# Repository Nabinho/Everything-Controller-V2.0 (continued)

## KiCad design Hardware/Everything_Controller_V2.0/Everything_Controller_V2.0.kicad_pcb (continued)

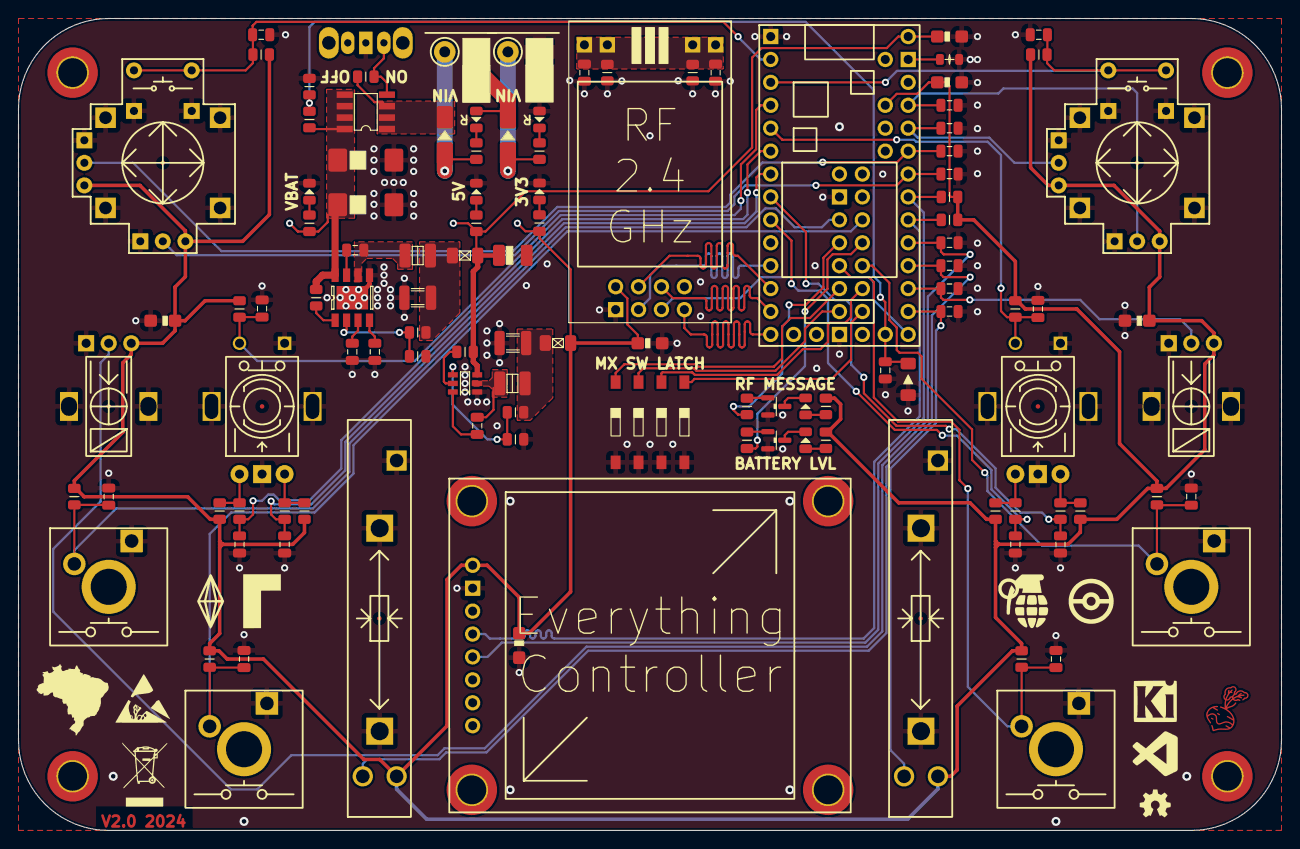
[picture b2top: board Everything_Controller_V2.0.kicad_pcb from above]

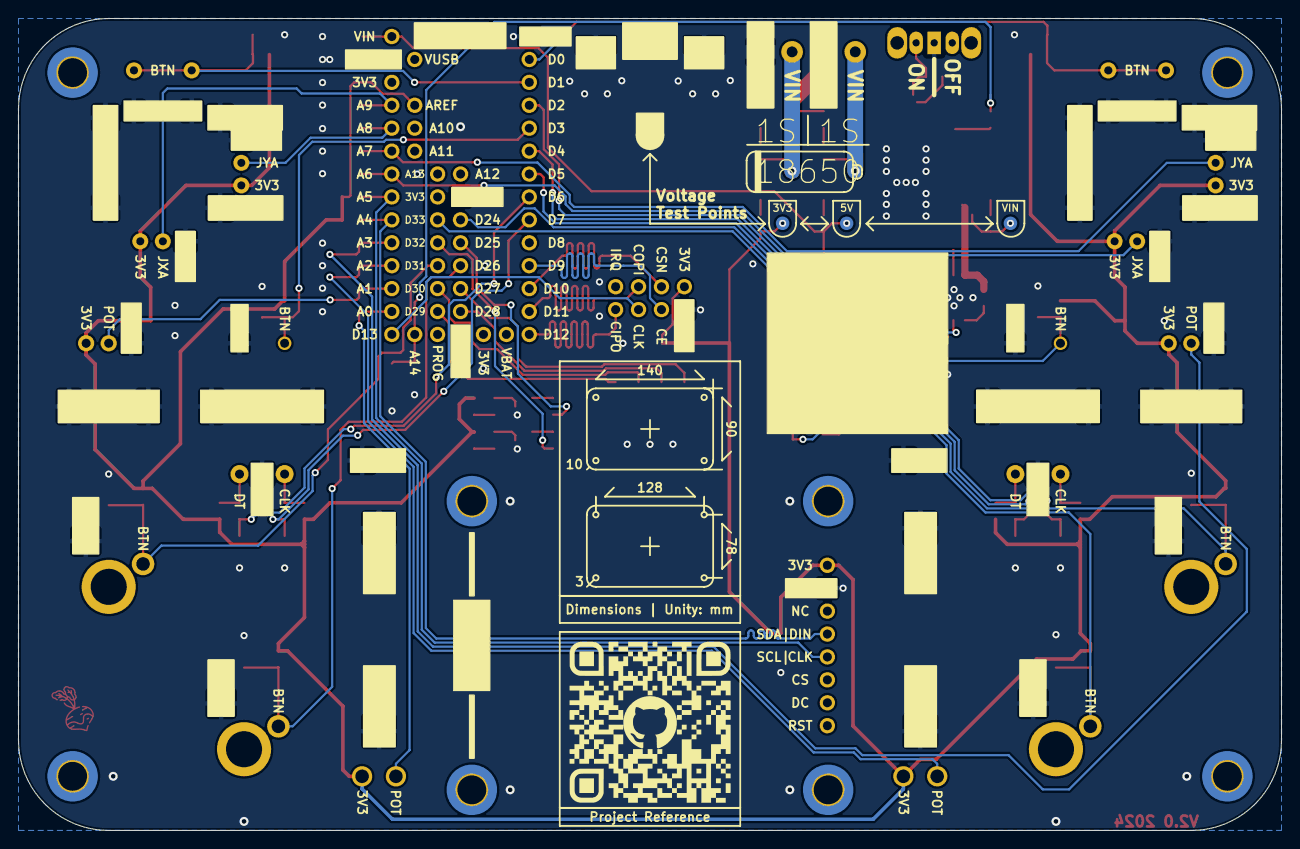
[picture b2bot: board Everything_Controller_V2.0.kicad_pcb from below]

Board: 2 copper layers, 140.0 x 90.0 mm, 119 parts (4 on the bottom side), 72 nets.

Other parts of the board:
C36: 10uF; CP_EIA-3528-21_Kemet-B
C37, C38: 100nF; C_0805_2012Metric

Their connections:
+5V: C36.1; also elsewhere on the board
GND: C36.2, C37.2, C38.2; also elsewhere on the board

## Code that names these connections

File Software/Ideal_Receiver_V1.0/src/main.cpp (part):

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#define PIN_PWM8 21

// PPM output pins configuration
#define PIN_PPM1 22
#define PIN_PPM2 23

// Digital output pins configuration
#define PIN_DOUT1 29
#define PIN_DOUT2 30
#define PIN_DOUT3 31
#define PIN_DOUT4 28
#define PIN_DOUT5 27
#define PIN_DOUT6 26
#define PIN_DOUT7 25
#define PIN_DOUT8 24

// LED output pins configuration
#define PIN_LED1 32
#define PIN_LED2 33

// Buttons pins configuration
#define PIN_BTN1 14
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
// NRF24L01 pins definitions
#define PIN_CE 9
#define PIN_CSN 10

// SSD1306 display definitions
#define DISPLAY_WIDTH 128
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ADC *adc = new ADC();

// NRF24L01 control object
RF24 radio(PIN_CE, PIN_CSN);

// SSD1306 display control object
Adafruit_SSD1306 display(DISPLAY_WIDTH, DISPLAY_HEIGHT, &Wire, DISPLYA_RESET);
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
// PPM pins definitions
const uint8_t NUMBER_PPM = 2;
const uint8_t PPM_PINS[NUMBER_PPM] = {PIN_PPM1, PIN_PPM2};
uint16_t PPM_OUT[NUMBER_PPM] = {90, 90};

// Digital pins definitions
const uint8_t NUMBER_DOUTS = 8;
const uint8_t DOUT_PINS[NUMBER_DOUTS] = {PIN_DOUT1, PIN_DOUT2, PIN_DOUT3, PIN_DOUT4, PIN_DOUT5, PIN_DOUT6, PIN_DOUT7, PIN_DOUT8};
bool DOUT_OUT[NUMBER_DOUTS] = {0, 0, 0, 0, 0, 0, 0, 0};

// LEDs Pins
const uint8_t NUMBER_LEDS = 2;
const uint8_t LED_PINS[NUMBER_LEDS] = {PIN_LED1, PIN_LED2};

// Controller buttons objects
const uint8_t NUMBER_BUTTONS = 4;
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
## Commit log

2024-03-24 README update
2024-03-24 minor corrections
2024-08-08 Ideal_Reaceiver
    Inclusion of the Ideal Receiver project.
2024-11-15 Better_Logic
    Better logic for controller and ideal receiver for better performance.
2024-11-15 Receiver_battery_reading
2025-01-21 Multi Translator Discontinued
2025-04-11 MovingAvg Inclusion
